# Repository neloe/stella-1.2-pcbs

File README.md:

# STELLA 1.2 Permaproto Replacement PCBs

These boards are designed to be drop in replacement for the full and half permaprotos used in the [NASA STELLA 1.2](https://science.gsfc.nasa.gov/stella/) project.
Not all modules are supported at this time.
STELLA-1.2 was created by Paul Mirel, NASA Goddard.

These KiCad projects were designed in KiCad 10; if the place you are having your boards fabricated do not support kicad_pcb files, you should generate the Gerber files with the options required by your fabricator, though some "generic" gerber/drl files will be provided at milestones in [Releases](https://github.com/neloe/stella-1.2-pcbs/releases).

## Assembly Instruction

You will need the same BOM as the full project, with the exception of the permaproto boards and wire.
The boards try to be as self documenting as possible with the silkscreens.
On the base board the build instructions have you placing components on both sides of the board.
The correct orientation and side is indicated with the silkscreens; a component's outline appears on the side of the board on which it should be placed; see the renderings below for an example.
On most components a pin (usually VCC/Vin/3v3 or GND) has been explicitly labelled; make sure that pin matches up with your breakout board.

Some boards have multiple footprints for the same component.
This includes (but may not be limited to in the future):

* Base PCB RTC Module
    * Both listed Adafruit SKUs use the same RTC chip but have different sizes; use whichever you are able to get in stock
* RS Spectral Sensor
    * The Triad sensor is EOL, though new stock may crop up from time to time
    * The replacement Adafruit spectral sensor should line up with the 3D printed case slot for the triad
* RS Temperature/Humidity
    * Due to parts availability, the HDC3022 module can be swapped for the SHT4x series; use the appropriate set of pins for whichever sensor is available

## Board Renderings

### Base PCB

### Remote Sensing module (RS)

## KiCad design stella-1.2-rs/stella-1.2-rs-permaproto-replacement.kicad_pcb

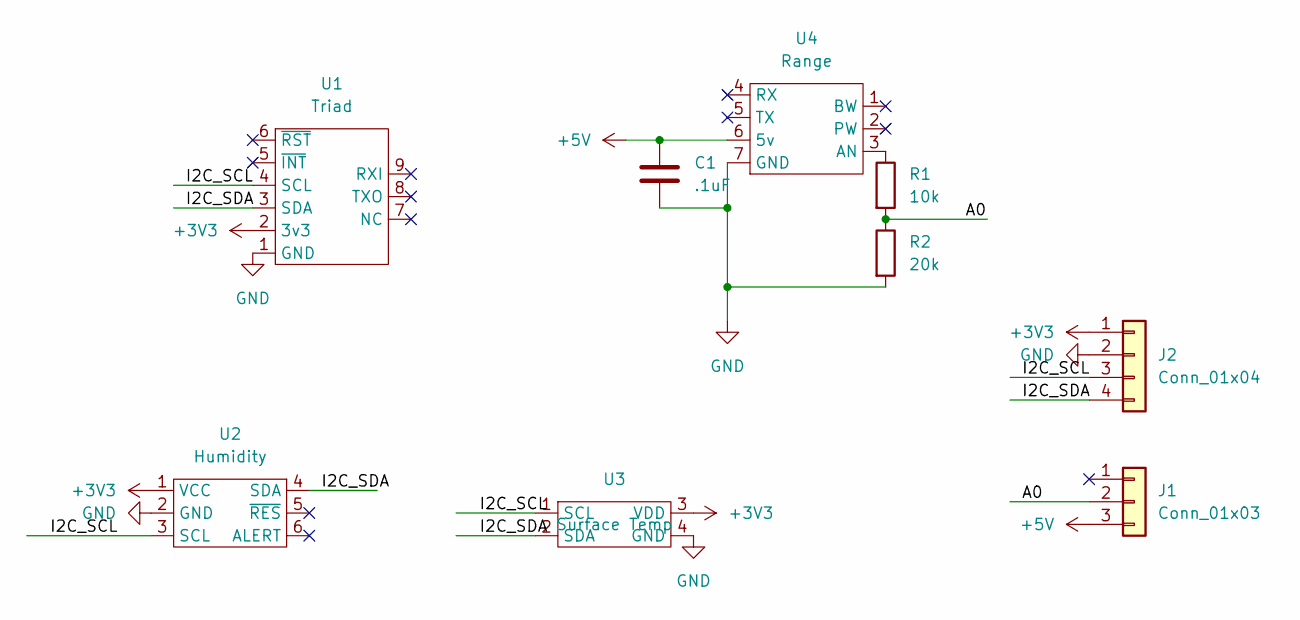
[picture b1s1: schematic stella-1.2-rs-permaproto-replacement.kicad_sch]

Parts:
C1: .1uF; C_Radial_D6.3mm_H5.0mm_P2.50mm
J1: Conn_01x03; MagConn-3P-M_5360
J2: Conn_01x04; MagConn-4P-M_5358
R1: 10k; R_Axial_DIN0204_L3.6mm_D1.6mm_P7.62mm_Horizontal
R2: 20k; R_Axial_DIN0204_L3.6mm_D1.6mm_P7.62mm_Horizontal
U1: Triad; Triad_sen15050
U2: Humidity; Humidity_5989
U3: Surface Temp; TO-39-4
U4: Range; Rangefinder_LV-EZ1

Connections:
+3V3: J2.1, U1.2 (3v3), U2.1 (VCC), U3.3 (VDD)
+5V: C1.1, J1.3, U4.6 (5v)
/A0: J1.2, R1.2, R2.1
/I2C_SCL: J2.3, U1.4 (SCL), U2.3 (SCL), U3.1 (SCL)
/I2C_SDA: J2.4, U1.3 (SDA), U2.4 (SDA), U3.2 (SDA)
GND: C1.2, J2.2, R2.2, U1.1 (GND), U2.2 (GND), U3.4 (GND), U4.7 (GND)
unnamed: R1.1, U4.3 (AN)

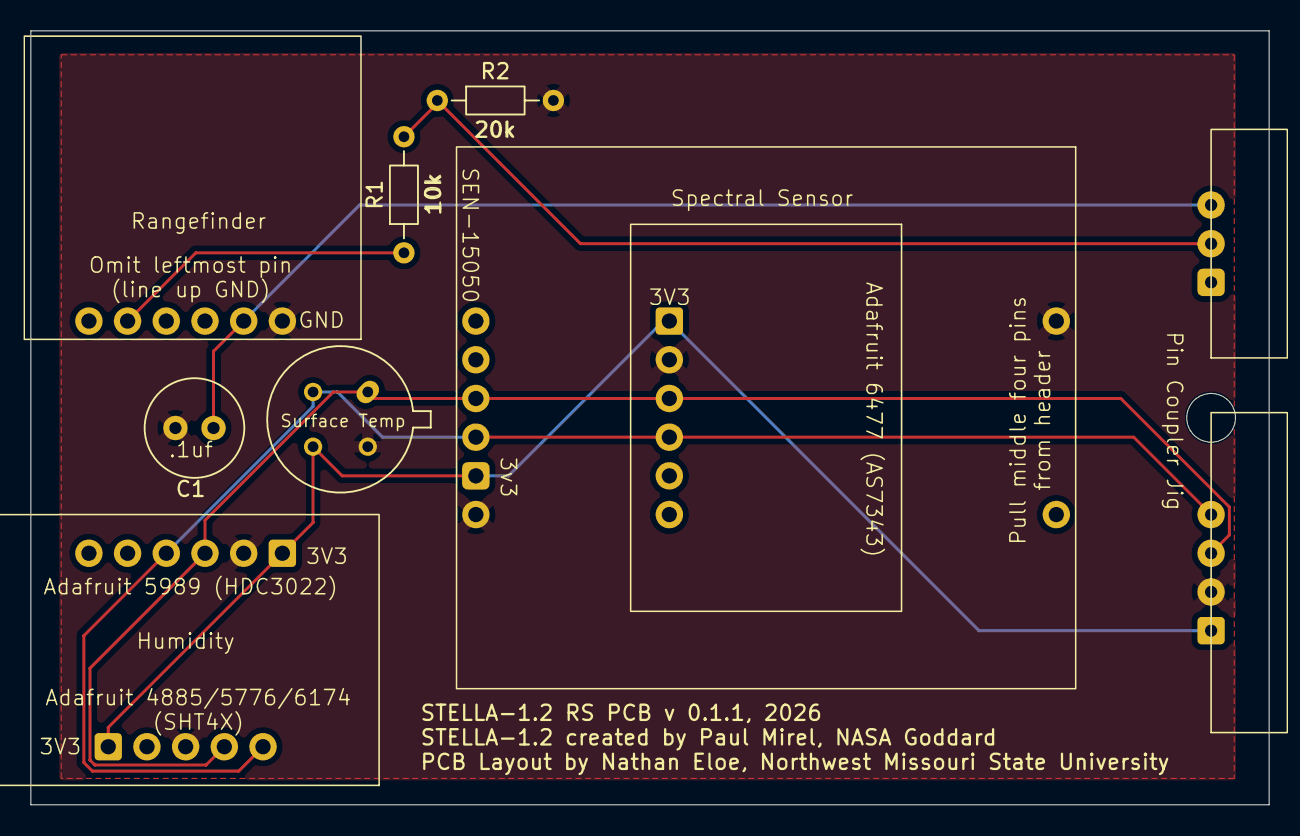
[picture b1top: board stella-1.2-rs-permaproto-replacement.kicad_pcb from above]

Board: 2 copper layers, 81.3 x 50.8 mm, 10 parts (0 on the bottom side), 7 nets.

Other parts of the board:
PinCouplerJig: MountingHole_3.2mm_M3

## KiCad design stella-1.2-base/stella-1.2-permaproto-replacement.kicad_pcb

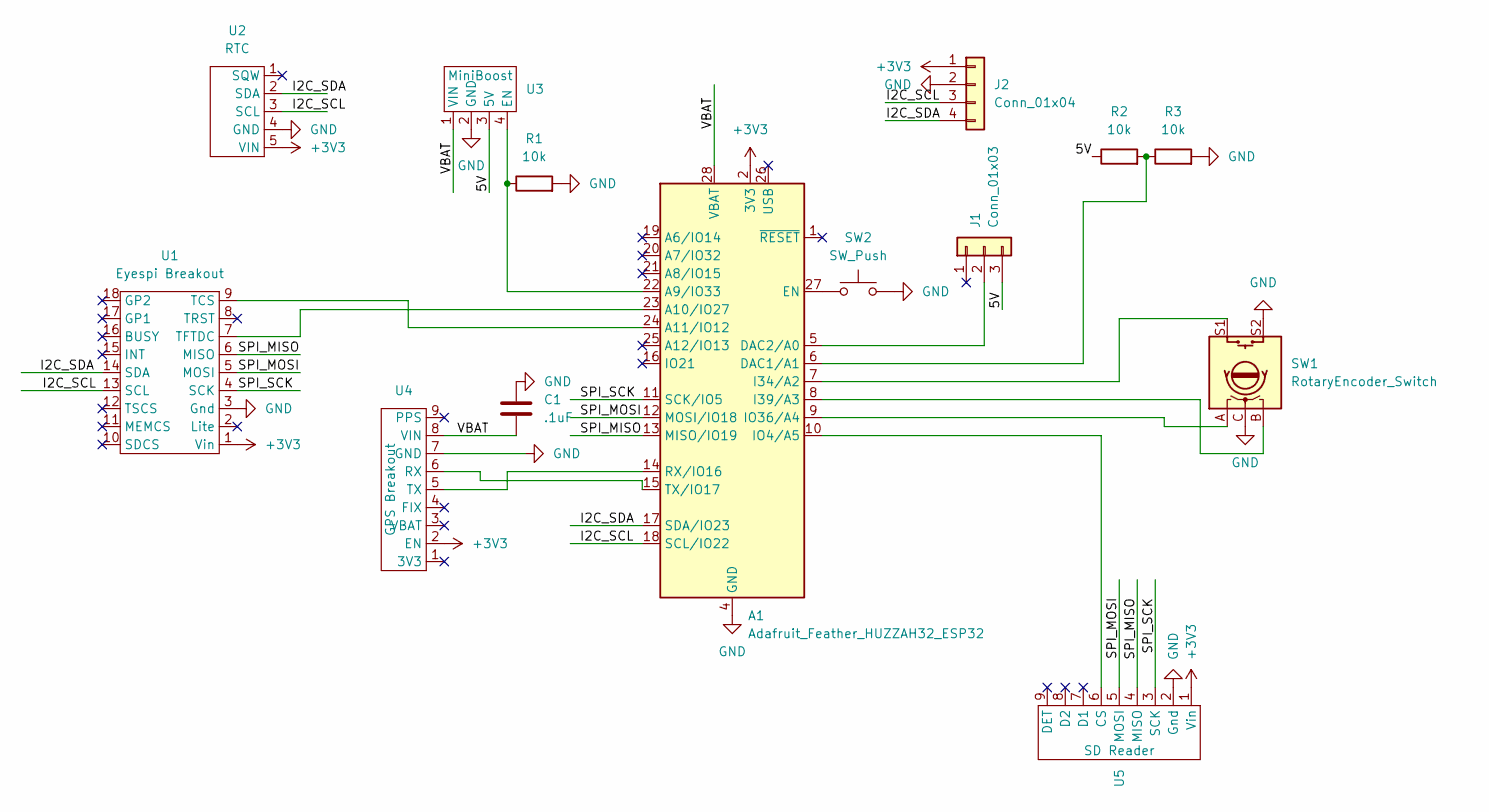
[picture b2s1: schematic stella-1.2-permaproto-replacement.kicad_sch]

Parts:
A1: Adafruit_Feather_HUZZAH32_ESP32; Adafruit_Feather
C1: .1uF; C_Radial_D6.3mm_H7.0mm_P2.50mm
J1: Conn_01x03; MagConn-3P-F_5360
J2: Conn_01x04; MagConn-4P-F_5358
R1, R2, R3: 10k; R_Axial_DIN0204_L3.6mm_D1.6mm_P7.62mm_Horizontal
SW1: RotaryEncoder_Switch; RotaryEncoder_Bourns_Vertical_PEC12R-3x17F-Sxxxx
SW2: SW_Push; SWITCH_03211B
U1: Eyespi Breakout; Eyespi_5613
U2: RTC; RTC_5198_3295
U3: MiniBoost; MiniBoost_4654
U4: GPS Breakout; GPS_5440
U5: SD Reader; SDCard_4682

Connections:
+3V3: A1.2 (3V3), J2.1, U1.1 (Vin), U2.5 (VIN), U4.2 (EN), U5.1 (Vin)
/5V: J1.3, R2.1, U3.3 (5V)
/I2C_SCL: A1.18 (SCL/IO22), J2.3, U1.13 (SCL), U2.3 (SCL)
/I2C_SDA: A1.17 (SDA/IO23), J2.4, U1.14 (SDA), U2.2 (SDA)
/SPI_MISO: A1.13 (MISO/IO19), U1.6 (MISO), U5.4 (MISO)
/SPI_MOSI: A1.12 (MOSI/IO18), U1.5 (MOSI), U5.5 (MOSI)
/SPI_SCK: A1.11 (SCK/IO5), U1.4 (SCK), U5.3 (SCK)
/VBAT: A1.28 (VBAT), C1.2, U3.1 (VIN), U4.8 (VIN)
GND: A1.4 (GND), C1.1, J2.2, R1.2, R3.2, SW1.C, SW1.S2, SW2.2, U1.3 (Gnd), U2.4 (GND), U3.2 (GND), U4.7 (GND), U5.2 (Gnd)
unnamed: A1.22 (A9/IO33), R1.1, U3.4 (EN)
unnamed: A1.23 (A10/IO27), U1.7 (TFTDC)
unnamed: A1.24 (A11/IO12), U1.9 (TCS)
unnamed: A1.6 (DAC1/A1), R2.2, R3.1
unnamed: A1.5 (DAC2/A0), J1.2
unnamed: A1.27 (EN), SW2.1
unnamed: A1.7 (I34/A2), SW1.S1
unnamed: A1.8 (I39/A3), SW1.B
unnamed: A1.10 (IO4/A5), U5.6 (CS)
unnamed: A1.9 (IO36/A4), SW1.A
unnamed: A1.14 (RX/IO16), U4.5 (TX)
unnamed: A1.15 (TX/IO17), U4.6 (RX)

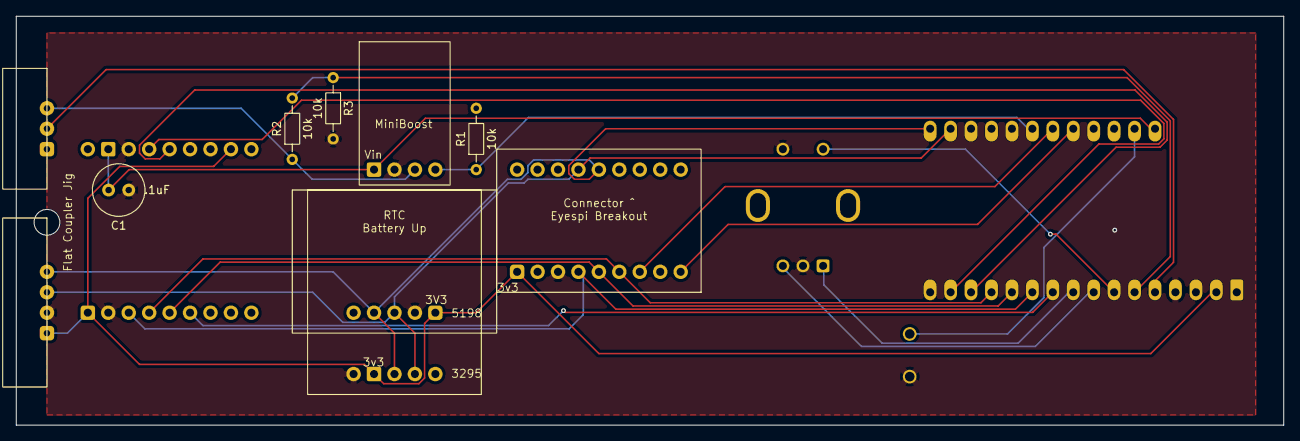
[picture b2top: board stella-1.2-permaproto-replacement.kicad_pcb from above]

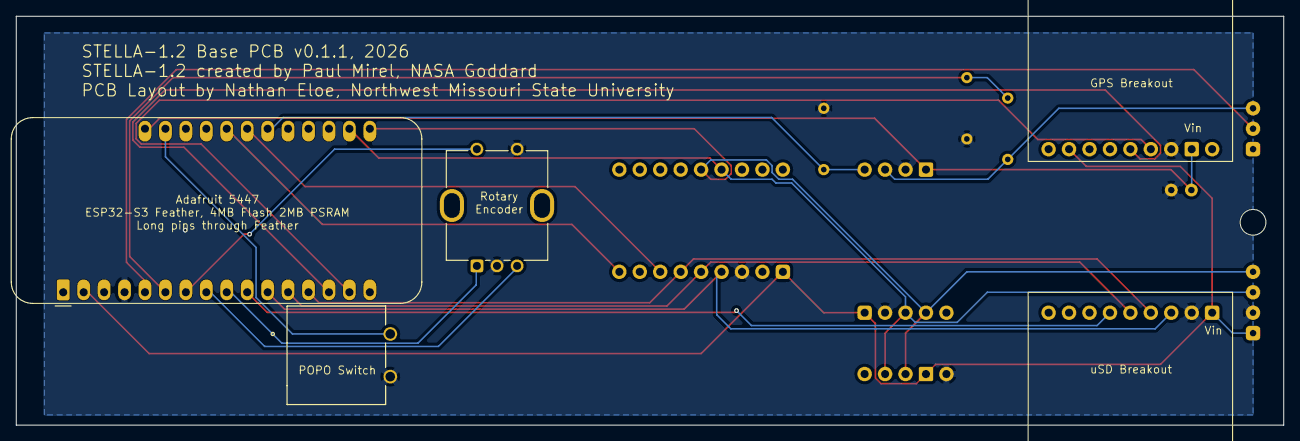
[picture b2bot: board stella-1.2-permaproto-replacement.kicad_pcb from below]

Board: 2 copper layers, 157.5 x 50.8 mm, 15 parts (5 on the bottom side), 21 nets.

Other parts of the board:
FlatCouplerJig: MountingHole_3.2mm_M3
